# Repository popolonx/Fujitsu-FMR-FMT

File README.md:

# FujitsuFMR
stuff for fmr and fm towns

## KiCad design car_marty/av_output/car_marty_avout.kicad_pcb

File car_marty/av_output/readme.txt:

audio and video output pcb for car marty

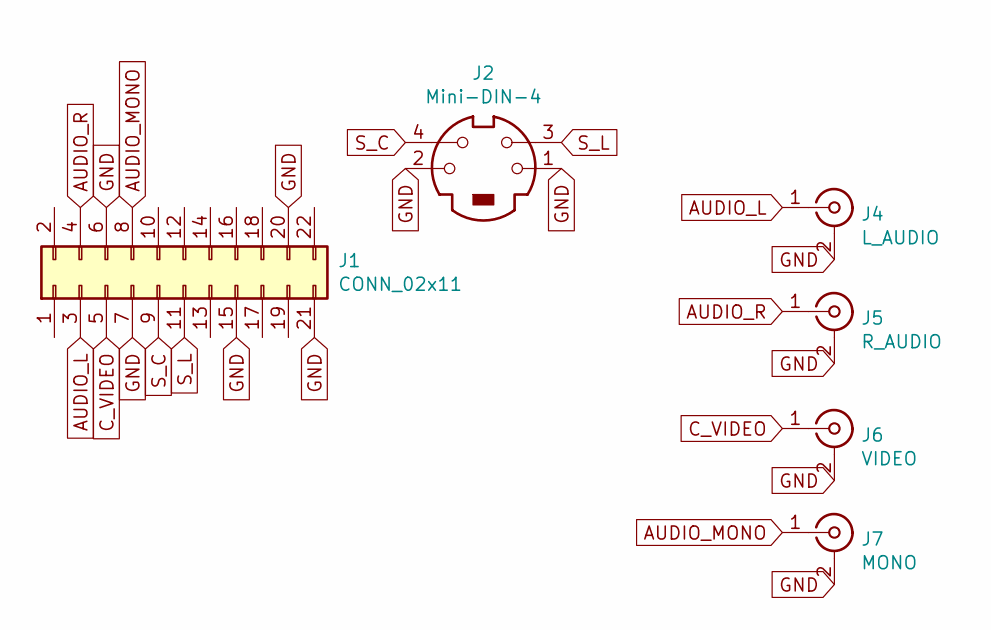
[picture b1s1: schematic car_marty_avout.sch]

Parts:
J1: CONN_02x11; PinHeader_2x11_P2.00mm_Vertical
J2: Mini-DIN-4; Mini_din4tme
J4: L_AUDIO; rca_audio
J5: R_AUDIO; rca_audio
J6: VIDEO; rca_audio
J7: MONO; rca_audio

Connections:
AUDIO_L: J1.3, J4.1 (In)
AUDIO_MONO: J1.8, J7.1 (In)
AUDIO_R: J1.4, J5.1 (In)
C_VIDEO: J1.5, J6.1 (In)
GND: J1.6, J1.7, J1.15, J1.20, J1.21, J2.1, J2.2, J4.2 (Ext), J5.2 (Ext), J6.2 (Ext), J7.2 (Ext)
S_C: J1.9, J2.4
S_L: J1.11, J2.3

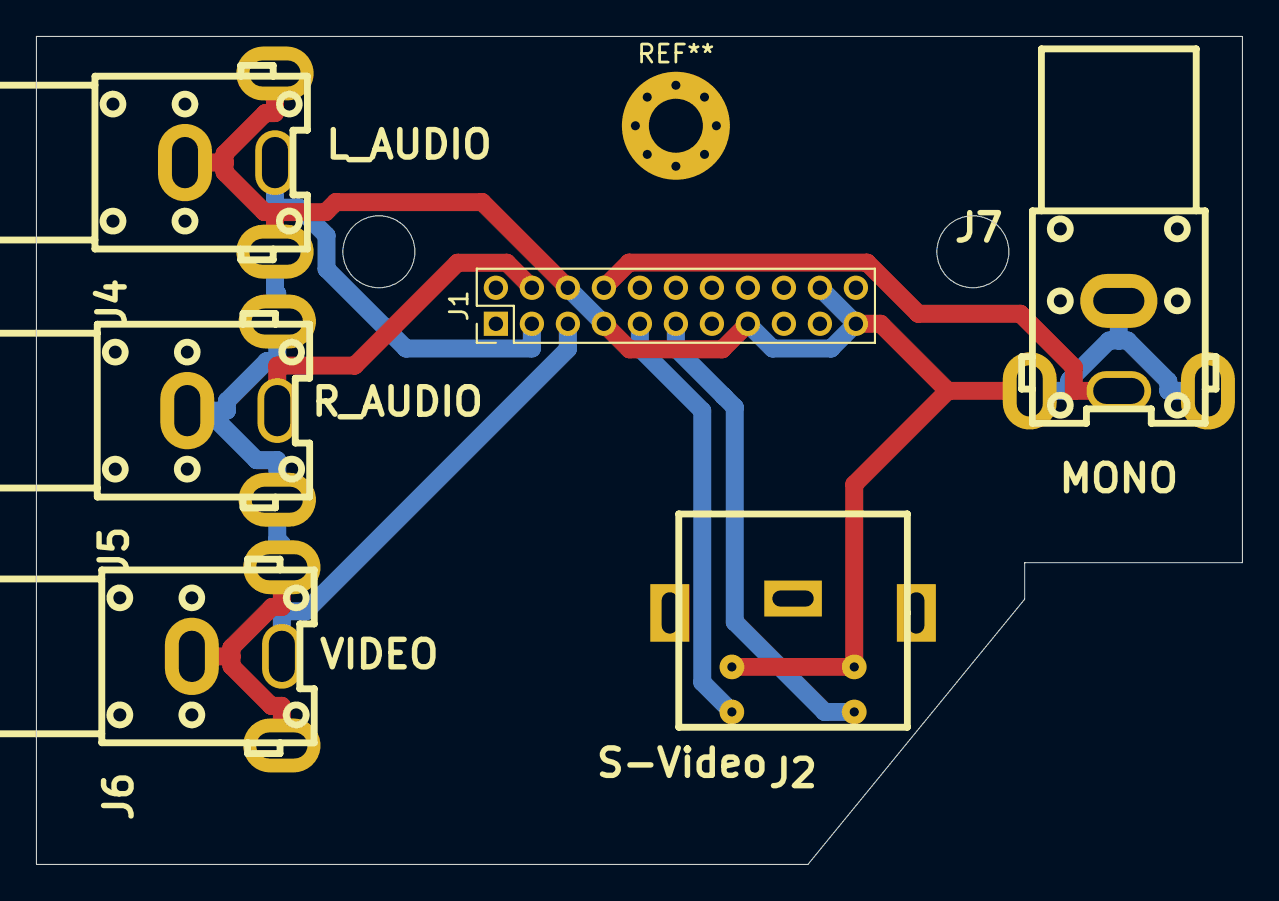
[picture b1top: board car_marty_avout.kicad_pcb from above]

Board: 2 copper layers, 67.0 x 46.0 mm, 6 parts (0 on the bottom side), 7 nets.

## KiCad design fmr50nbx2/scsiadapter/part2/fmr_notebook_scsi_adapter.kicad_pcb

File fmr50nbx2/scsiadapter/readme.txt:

two pcbs to connect 2.5" scsi drive (40 + 8 pins) to fmr50nbx2 side connector (scsi like 50 pin connector)
parts needed:
-scsi connector from https://www.aliexpress.com/item/33045463648.html  , need to remove the metal shield away from it
-25x2 2mm pitch female pin header 
-long 2mm pitch pin headers, for example https://www.aliexpress.com/item/32767743885

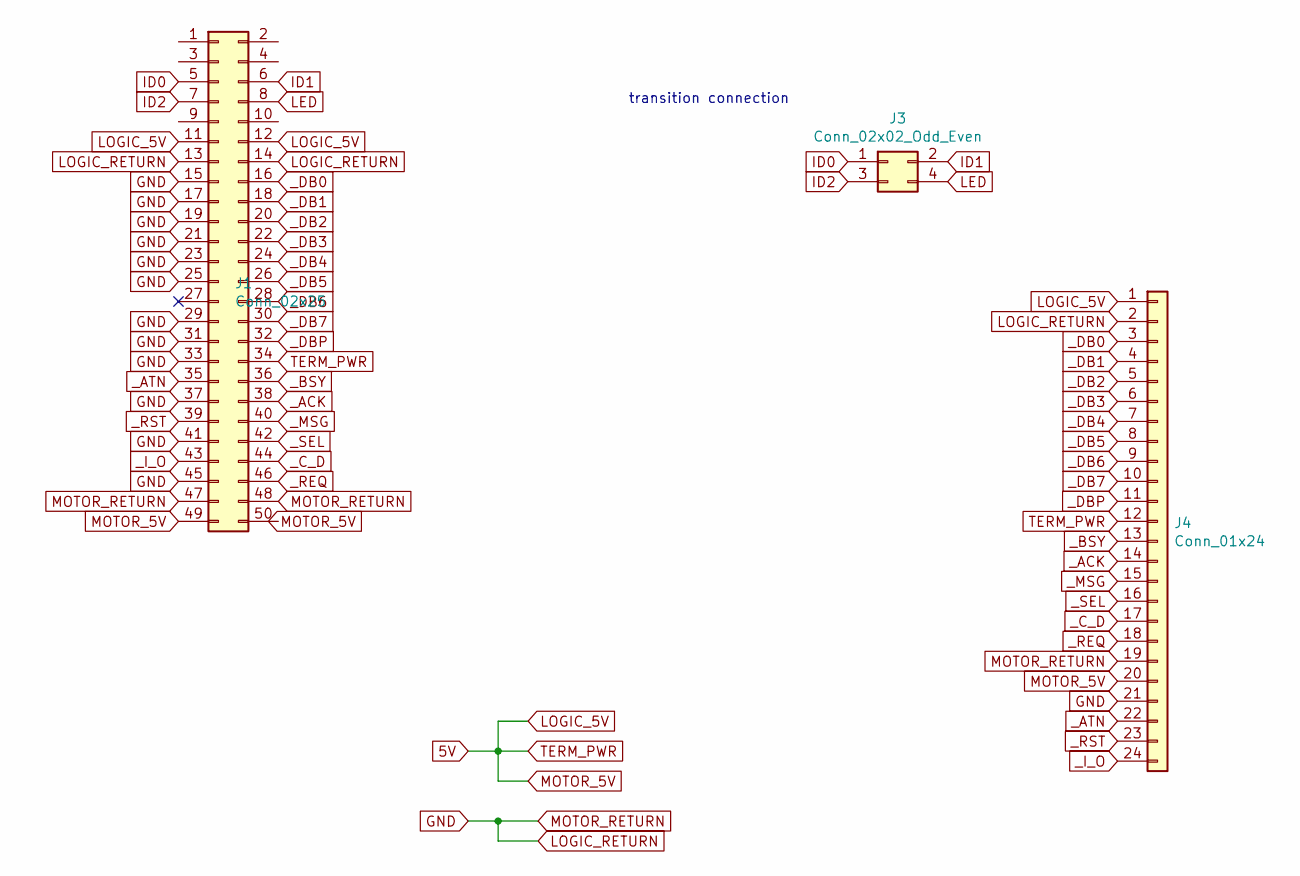
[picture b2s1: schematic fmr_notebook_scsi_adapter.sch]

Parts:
J1: Conn_02x25; PinHeader_2x25_P2.00mm_Vertical
J3: Conn_02x02_Odd_Even; PinHeader_2x02_P2.00mm_Vertical
J4: Conn_01x24; PinHeader_1x24_P2.00mm_Vertical

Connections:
5V: J1.11, J1.12, J1.34, J1.49, J4.1, J4.12, J4.20
GND: J1.13, J1.14, J1.15, J1.17, J1.19, J1.21, J1.23, J1.25, J1.29, J1.31, J1.33, J1.37, J1.41, J1.45, J1.47, J1.48, J4.2, J4.19, J4.21
ID0: J1.5, J3.1
ID1: J1.6, J3.2
ID2: J1.7, J3.3
LED: J1.8, J3.4
_ACK: J1.38, J4.14
_ATN: J1.35, J4.22
_BSY: J1.36, J4.13
_C_D: J1.44, J4.17
_DB0: J1.16, J4.3
_DB1: J1.18, J4.4
_DB2: J1.20, J4.5
_DB3: J1.22, J4.6
_DB4: J1.24, J4.7
_DB5: J1.26, J4.8
_DB6: J1.28, J4.9
_DB7: J1.30, J4.10
_DBP: J1.32, J4.11
_I_O: J1.43, J4.24
_MSG: J1.40, J4.15
_REQ: J1.46, J4.18
_RST: J1.39, J4.23
_SEL: J1.42, J4.16

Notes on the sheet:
transition connection

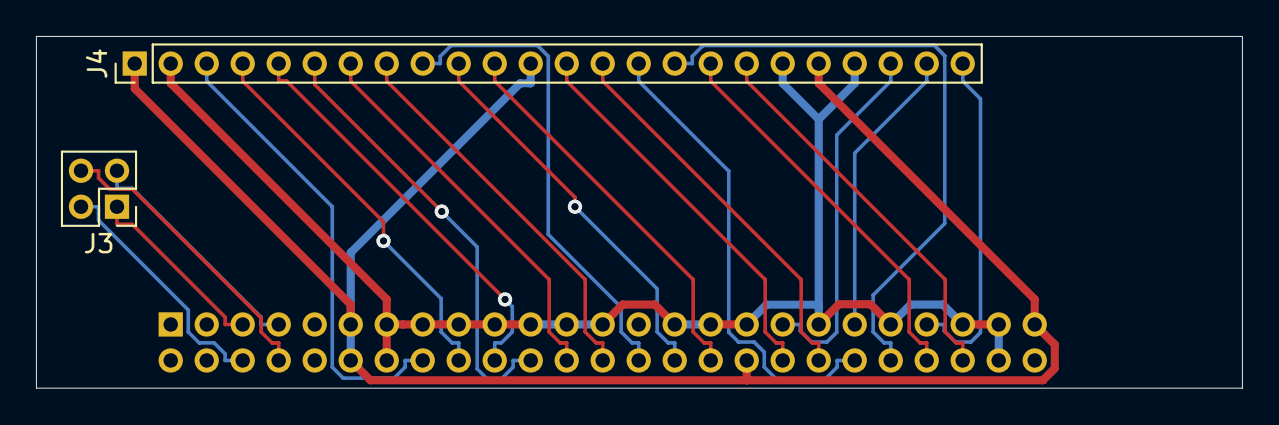
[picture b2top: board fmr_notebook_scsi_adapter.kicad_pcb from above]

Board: 2 copper layers, 67.0 x 19.5 mm, 3 parts (1 on the bottom side), 24 nets.
